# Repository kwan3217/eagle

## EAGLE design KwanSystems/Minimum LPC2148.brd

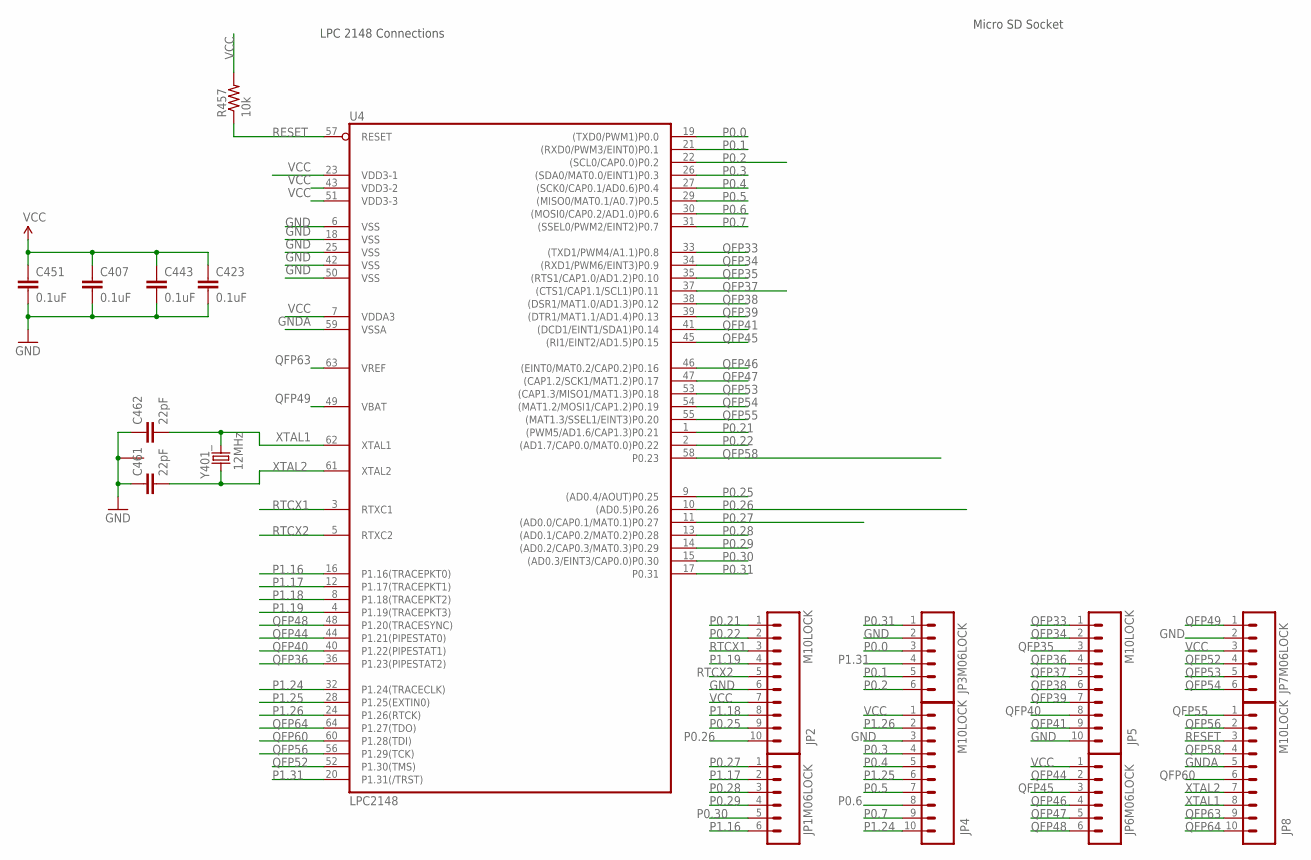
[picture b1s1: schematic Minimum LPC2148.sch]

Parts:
C407, C423, C443, C451: 0.1uF; 0402-CAP
C461, C462: 22pF; 0402-CAP
JP1, JP3, JP6, JP7: M06LOCK; 1X06_LOCK
JP2, JP4, JP5, JP8: M10LOCK; 1X10_LOCK
R457: 10k; 0402-RES
U4: LPC2148; SQFP-S-10X10-64
Y401: 12MHz; CRYSTAL_SMD

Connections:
GND: C407.2, C423.2, C443.2, C451.2, C461.1, C462.1, JP2.6, JP3.2, JP4.3, JP5.10, JP7.2, U4.6 (VSS), U4.18 (VSS), U4.25 (VSS), U4.42 (VSS), U4.50 (VSS), Y401.2 (1), Y401.4 (1)
GNDA: JP8.5, U4.59 (VSSA)
P0.0: JP3.3, U4.19 ((TXD0/PWM1)P0.0)
P0.1: JP3.5, U4.21 ((RXD0/PWM3/EINT0)P0.1)
P0.2: JP3.6, U4.22 ((SCL0/CAP0.0)P0.2)
P0.3: JP4.4, U4.26 ((SDA0/MAT0.0/EINT1)P0.3)
P0.4: JP4.5, U4.27 ((SCK0/CAP0.1/AD0.6)P0.4)
P0.5: JP4.7, U4.29 ((MISO0/MAT0.1/A0.7)P0.5)
P0.6: JP4.8, U4.30 ((MOSI0/CAP0.2/AD1.0)P0.6)
P0.7: JP4.9, U4.31 ((SSEL0/PWM2/EINT2)P0.7)
P0.21: JP2.1, U4.1 ((PWM5/AD1.6/CAP1.3)P0.21)
P0.22: JP2.2, U4.2 ((AD1.7/CAP0.0/MAT0.0)P0.22)
P0.25: JP2.9, U4.9 ((AD0.4/AOUT)P0.25)
P0.26: JP2.10, U4.10 ((AD0.5)P0.26)
P0.27: JP1.1, U4.11 ((AD0.0/CAP0.1/MAT0.1)P0.27)
P0.28: JP1.3, U4.13 ((AD0.1/CAP0.2/MAT0.2)P0.28)
P0.29: JP1.4, U4.14 ((AD0.2/CAP0.3/MAT0.3)P0.29)
P0.30: JP1.5, U4.15 ((AD0.3/EINT3/CAP0.0)P0.30)
P0.31: JP3.1, U4.17 (P0.31)
P1.16: JP1.6, U4.16 (P1.16(TRACEPKT0))
P1.17: JP1.2, U4.12 (P1.17(TRACEPKT1))
P1.18: JP2.8, U4.8 (P1.18(TRACEPKT2))
P1.19: JP2.4, U4.4 (P1.19(TRACEPKT3))
P1.24: JP4.10, U4.32 (P1.24(TRACECLK))
P1.25: JP4.6, U4.28 (P1.25(EXTIN0))
P1.26: JP4.2, U4.24 (P1.26(RTCK))
P1.31: JP3.4, U4.20 (P1.31(/TRST))
QFP33: JP5.1, U4.33 ((TXD1/PWM4/A1.1)P0.8)
QFP34: JP5.2, U4.34 ((RXD1/PWM6/EINT3)P0.9)
QFP35: JP5.3, U4.35 ((RTS1/CAP1.0/AD1.2)P0.10)
QFP36: JP5.4, U4.36 (P1.23(PIPESTAT2))
QFP37: JP5.5, U4.37 ((CTS1/CAP1.1/SCL1)P0.11)
QFP38: JP5.6, U4.38 ((DSR1/MAT1.0/AD1.3)P0.12)
QFP39: JP5.7, U4.39 ((DTR1/MAT1.1/AD1.4)P0.13)
QFP40: JP5.8, U4.40 (P1.22(PIPESTAT1))
QFP41: JP5.9, U4.41 ((DCD1/EINT1/SDA1)P0.14)
QFP44: JP6.2, U4.44 (P1.21(PIPESTAT0))
QFP45: JP6.3, U4.45 ((RI1/EINT2/AD1.5)P0.15)
QFP46: JP6.4, U4.46 ((EINT0/MAT0.2/CAP0.2)P0.16)
QFP47: JP6.5, U4.47 ((CAP1.2/SCK1/MAT1.2)P0.17)
QFP48: JP6.6, U4.48 (P1.20(TRACESYNC))
QFP49: JP7.1, U4.49 (VBAT)
QFP52: JP7.4, U4.52 (P1.30(TMS))
QFP53: JP7.5, U4.53 ((CAP1.3/MISO1/MAT1.3)P0.18)
QFP54: JP7.6, U4.54 ((MAT1.2/MOSI1/CAP1.2)P0.19)
QFP55: JP8.1, U4.55 ((MAT1.3/SSEL1/EINT3)P0.20)
QFP56: JP8.2, U4.56 (P1.29(TCK))
QFP58: JP8.4, U4.58 (P0.23)
QFP60: JP8.6, U4.60 (P1.28(TDI))
QFP63: JP8.9, U4.63 (VREF)
QFP64: JP8.10, U4.64 (P1.27(TDO))
RESET: JP8.3, R457.1, U4.57 (RESET)
RTCX1: JP2.3, U4.3 (RTXC1)
RTCX2: JP2.5, U4.5 (RTXC2)
VCC: C407.1, C423.1, C443.1, C451.1, JP2.7, JP4.1, JP6.1, JP7.3, R457.2, U4.7 (VDDA3), U4.23 (VDD3-1), U4.43 (VDD3-2), U4.51 (VDD3-3)
XTAL1: C462.2, JP8.8, U4.62 (XTAL1), Y401.3 (2)
XTAL2: C461.2, JP8.7, U4.61 (XTAL2), Y401.1

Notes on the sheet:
Micro SD Socket
LPC 2148 Connections

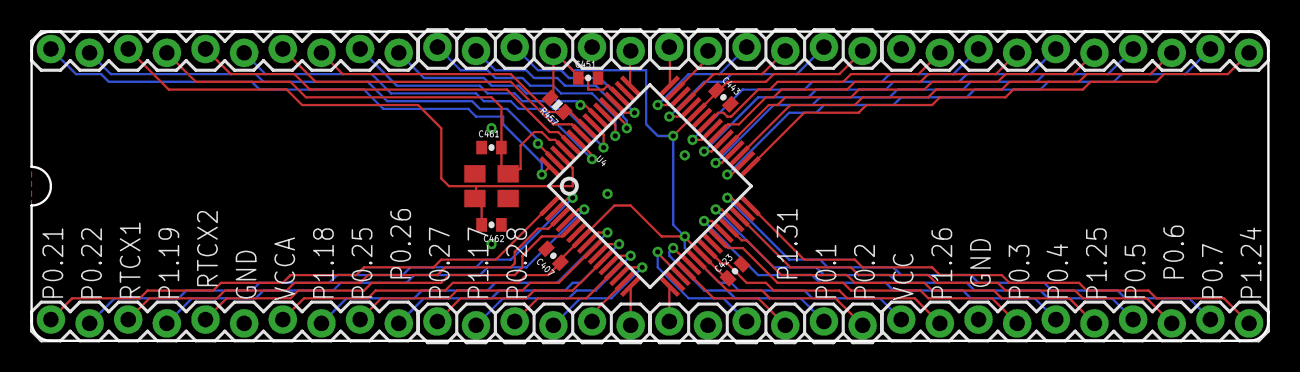
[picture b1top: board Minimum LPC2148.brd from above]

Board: 2 copper layers, 81.3 x 20.3 mm, 17 parts (0 on the bottom side), 57 nets.

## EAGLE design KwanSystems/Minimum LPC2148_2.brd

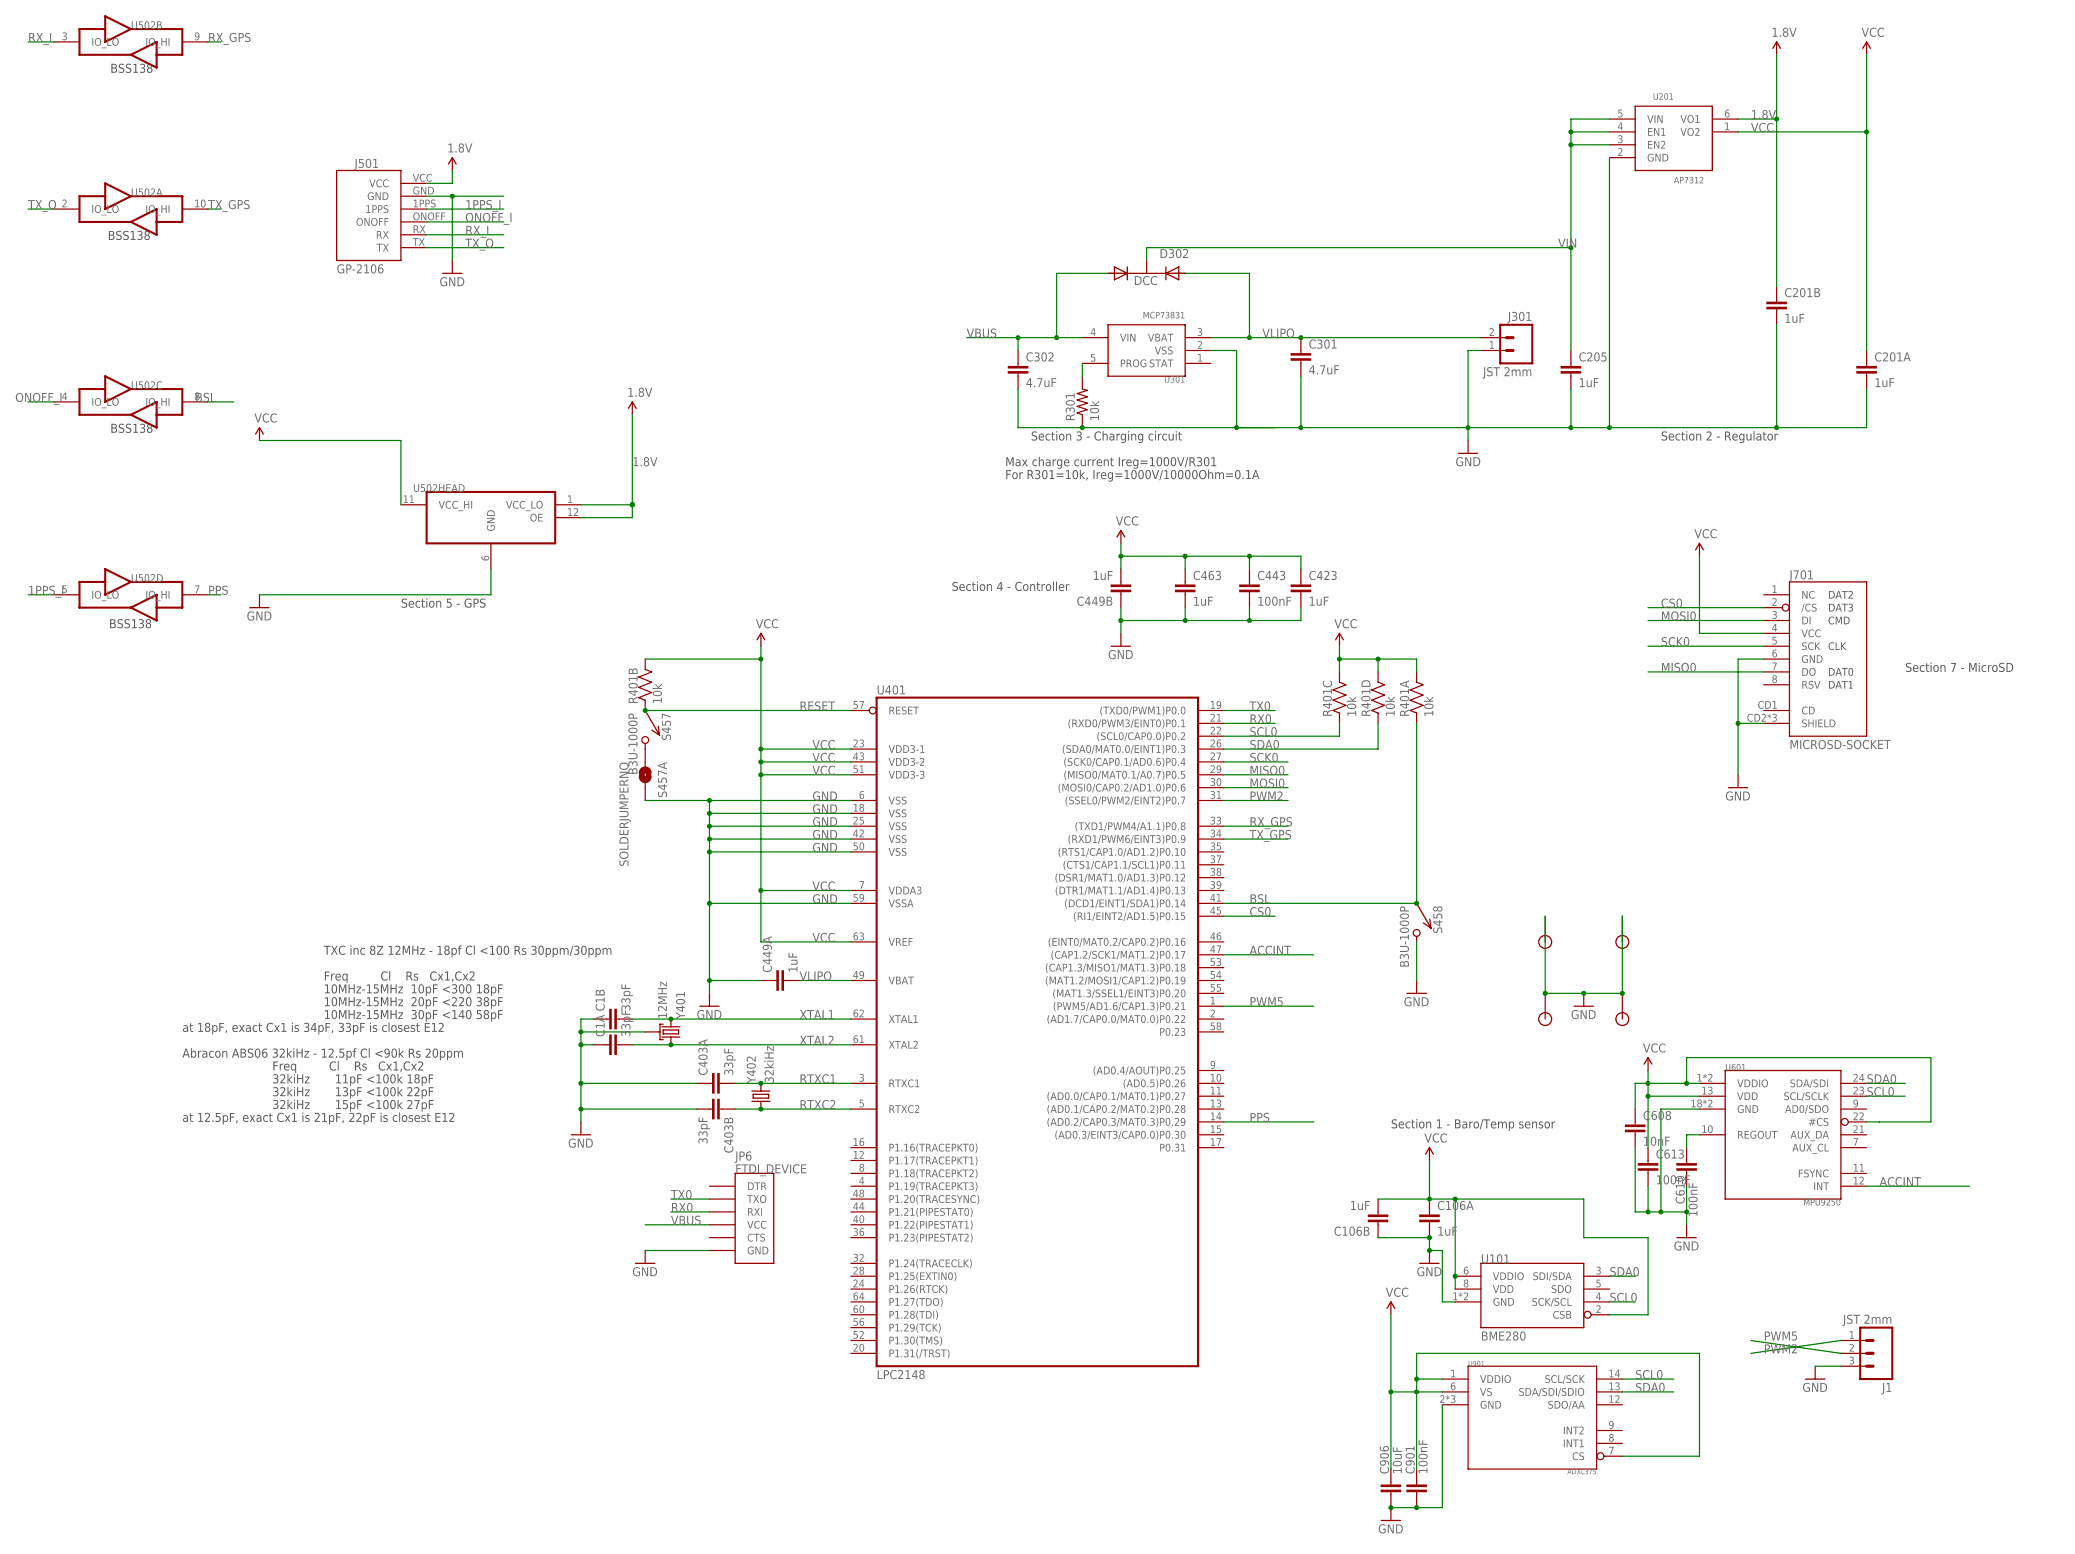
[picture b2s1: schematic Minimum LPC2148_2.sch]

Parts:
C1, C403: 33pF; CKCM25
C106, C201, C449: 1uF; CKCM25
C205, C423, C463: 1uF; 0402-CAP; DIGIKEY 445-4114-1-ND
C301, C302: 4.7uF; 0402-CAP; DIGIKEY 445-7395-1-ND
C443, C610, C613, C901: 100nF; 0402-CAP; DIGIKEY 445-1265-1-ND
C608: 10nF; 0402-CAP; DIGIKEY 445-1257-1-ND
C906: 10uF; 0603-CAP; DIGIKEY 445-7486-1-ND
D302: DCC; SOT-23-3; DIGIKEY 568-6500-1-ND
J1: JST 2mm; 1X03_NO_SILK; DIGIKEY 455-1749-1-ND
J301: JST 2mm; 1X02_NO_SILK; DIGIKEY 455-1749-1-ND
J501: GP-2106
J701: MICROSD-SOCKET; MICROSD-SOCKET-PP; DIGIKEY 101-00581-59-1-ND
JP1, JP2, JP4, JP5: STANDOFF; DIGIKEY $NOPART
JP6: FTDI_DEVICE; FTDI_DEVICE_SIDE
R301: 10k; 0402-RES; DIGIKEY P10.0KLCT-ND
R401: 10k; CRA04; DIGIKEY CRA4S810KCT-ND
S457, S458: B3U-1000P; DIGIKEY SW1020CT-ND
S457A: SOLDERJUMPERNO; SJ_2S-NO; DIGIKEY $NOPART
U101: BME280
U201: AP7312; SOT-23-6
U301: MCP73831; SOT-23-5; DIGIKEY 576-1910-1-ND
U401: LPC2148; SQFP-S-10X10-64; DIGIKEY 568-1765-ND
U502: TXB0104RUT; R-PUQFN-N12
U601: MPU9250; LQFN_3MM_3MM
U901: ADXL375
Y401: 12MHz; CRYSTAL_SMD_2MM_2_5MM; DIGIKEY 887-1487-1-ND
Y402: 32kiHz; ABS06; DIGIKEY 535-10104-1-ND

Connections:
1.8V: C201.2 (1), J501.VCC, U201.6 (VO1), U502.1 (VCC_LO), U502.12 (OE)
1PPS_I: J501.1PPS, U502.5 (IO_LO)
ACCINT: U401.47 ((CAP1.2/SCK1/MAT1.2)P0.17), U601.12 (INT)
BSL: R401.1, S458.P$1 (1), U401.41 ((DCD1/EINT1/SDA1)P0.14), U502.8 (IO_HI)
CS0: J701.2 (/CS), U401.45 ((RI1/EINT2/AD1.5)P0.15)
GND: C1.1, C1.2 (1), C106.2 (1), C106.4 (2), C201.3 (2), C201.4 (2), C205.2, C301.2, C302.2, C403.1, C403.3 (2), C423.2, C443.2, C449.1, C449.2 (1), C463.2, C608.2, C610.2, C613.2, C901.2, C906.2, J1.3, J301.1, J501.GND, J701.6 (GND), J701.CD2 (SHIELD), J701.GND1 (SHIELD), J701.GND3 (SHIELD), JP1.P$1, JP2.P$1, JP4.P$1, JP5.P$1, JP6.P$6 (GND), R301.1, S457A.2, S458.P$2 (2), U101.1 (GND), U101.7 (GND), U201.2 (GND), U301.2 (VSS), U401.6 (VSS), U401.18 (VSS), U401.25 (VSS), U401.42 (VSS), U401.50 (VSS), U401.59 (VSSA), U502.6 (GND), U601.18 (GND), U601.20 (GND), U901.2 (GND), U901.4 (GND), U901.5 (GND), Y401.2 (GND), Y401.4 (GND)
MISO0: J701.7 (DO), U401.29 ((MISO0/MAT0.1/A0.7)P0.5)
MOSI0: J701.3 (DI), U401.30 ((MOSI0/CAP0.2/AD1.0)P0.6)
unnamed: R301.2, U301.5 (PROG)
unnamed: S457.P$2 (2), S457A.1
unnamed: C610.1, U601.10 (REGOUT)
ONOFF_I: J501.ONOFF, U502.4 (IO_LO)
PPS: U401.14 ((AD0.2/CAP0.3/MAT0.3)P0.29), U502.7 (IO_HI)
PWM2: J1.1, U401.31 ((SSEL0/PWM2/EINT2)P0.7)
PWM5: J1.2, U401.1 ((PWM5/AD1.6/CAP1.3)P0.21)
RESET: R401.2 (1), S457.P$1 (1), U401.57 (RESET)
RTXC1: C403.4 (2), U401.3 (RTXC1), Y402.2
RTXC2: C403.2 (1), U401.5 (RTXC2), Y402.1
RX0: JP6.P$3 (RXI), U401.21 ((RXD0/PWM3/EINT0)P0.1)
RX_GPS: U401.33 ((TXD1/PWM4/A1.1)P0.8), U502.9 (IO_HI)
RX_I: J501.RX, U502.3 (IO_LO)
SCK0: J701.5 (SCK), U401.27 ((SCK0/CAP0.1/AD0.6)P0.4)
SCL0: R401.3 (1), U101.4 (SCK/SCL), U401.22 ((SCL0/CAP0.0)P0.2), U601.23 (SCL/SCLK), U901.14 (SCL/SCK)
SDA0: R401.4 (1), U101.3 (SDI/SDA), U401.26 ((SDA0/MAT0.0/EINT1)P0.3), U601.24 (SDA/SDI), U901.13 (SDA/SDI/SDIO)
TX0: JP6.P$2 (TXO), U401.19 ((TXD0/PWM1)P0.0)
TX_GPS: U401.34 ((RXD1/PWM6/EINT3)P0.9), U502.10 (IO_HI)
TX_O: J501.TX, U502.2 (IO_LO)
VBUS: C302.1, D302.1 (A1), JP6.P$4 (VCC), U301.4 (VIN)
VCC: C106.1, C106.3 (2), C201.1, C423.1, C443.1, C449.3 (2), C463.1, C608.1, C613.1, C901.1, C906.1, J701.4 (VCC), R401.5 (2), R401.6 (2), R401.7 (2), R401.8 (2), U101.2 (CSB), U101.6 (VDDIO), U101.8 (VDD), U201.1 (VO2), U401.7 (VDDA3), U401.23 (VDD3-1), U401.43 (VDD3-2), U401.51 (VDD3-3), U401.63 (VREF), U502.11 (VCC_HI), U601.1 (VDDIO), U601.8 (VDDIO), U601.13 (VDD), U601.22 (#CS), U901.1 (VDDIO), U901.6 (VS), U901.7 (CS)
VIN: C205.1, D302.3 (K), U201.3 (EN2), U201.4 (EN1), U201.5 (VIN)
VLIPO: C301.1, C449.4 (2), D302.2 (A2), J301.2, U301.3 (VBAT), U401.49 (VBAT)
XTAL1: C1.3 (2), U401.62 (XTAL1), Y401.3 (2)
XTAL2: C1.4 (2), U401.61 (XTAL2), Y401.1

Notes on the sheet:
Section 2 - Regulator
Section 4 - Controller
Section 7 - MicroSD
Section 1 - Baro/Temp sensor
Freq Cl Rs Cx1,Cx2
10MHz-15MHz 10pF <300 18pF
10MHz-15MHz 20pF <220 38pF
10MHz-15MHz 30pF <140 58pF
TXC inc 8Z 12MHz - 18pf Cl <100 Rs 30ppm/30ppm
at 18pF, exact Cx1 is 34pF, 33pF is closest E12
32kiHz 11pF <100k 18pF
32kiHz 13pF <100k 22pF
32kiHz 15pF <100k 27pF
Abracon ABS06 32kiHz - 12.5pf Cl <90k Rs 20ppm
at 12.5pF, exact Cx1 is 21pF, 22pF is closest E12
Section 3 - Charging circuit
Max charge current Ireg=1000V/R301
For R301=10k, Ireg=1000V/10000Ohm=0.1A
BSS138
Section 5 - GPS

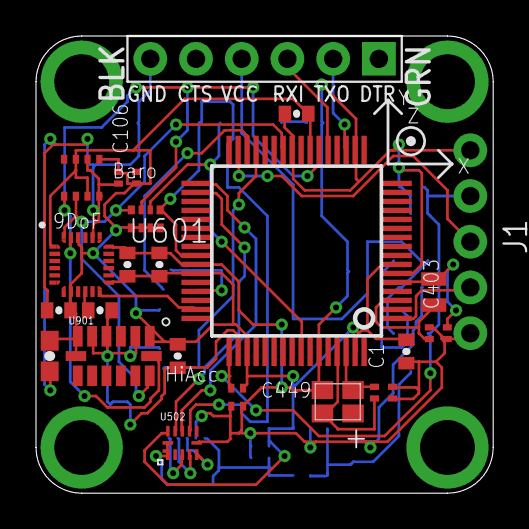
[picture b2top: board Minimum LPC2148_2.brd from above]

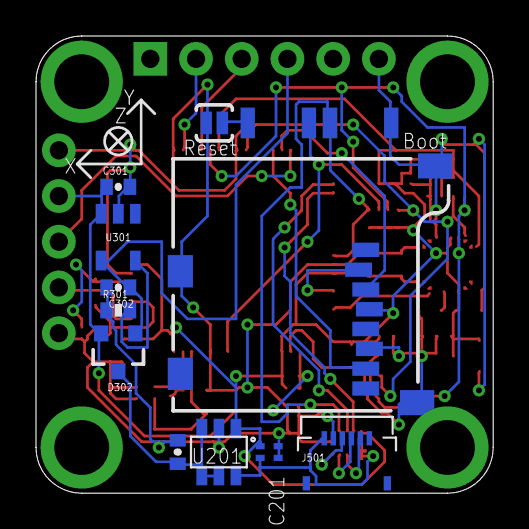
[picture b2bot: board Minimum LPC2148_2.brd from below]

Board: 2 copper layers, 25.4 x 25.4 mm, 41 parts (14 on the bottom side), 33 nets.

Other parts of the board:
U$4: AXES

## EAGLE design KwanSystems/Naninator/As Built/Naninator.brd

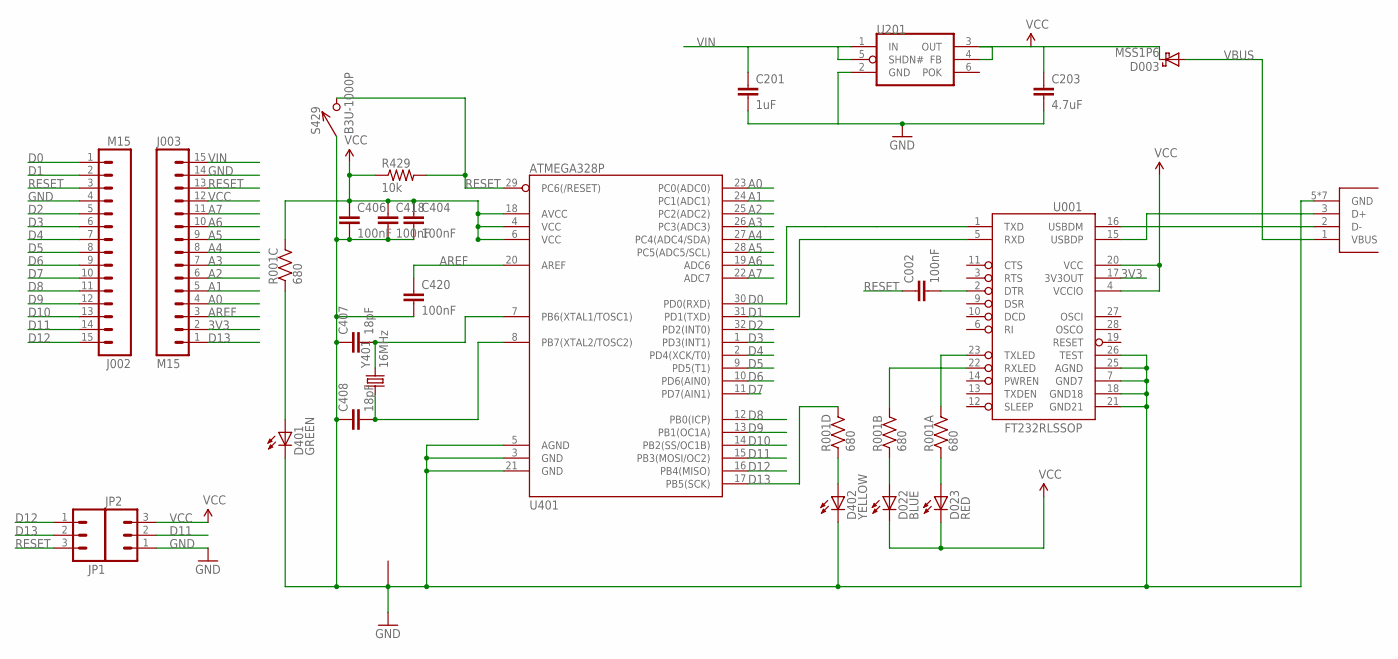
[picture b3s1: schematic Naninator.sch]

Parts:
C002, C404, C406, C418, C420: 100nF; 0402-CAP; DIGIKEY 445-1268-1-ND
C201: 1uF; 0402-CAP; DIGIKEY 445-1415-1-ND
C203: 4.7uF; 0402-CAP; DIGIKEY 445-7395-1-ND
C407, C408: 18pF; 0402-CAP; DIGIKEY 445-1238-1-ND
D003: MSS1P6; MICROSMP; DIGIKEY MSS1P6-M3/89AGICT-ND
D022: BLUE; LED-0603; DIGIKEY 350-2037-1-ND
D023: RED; LED-0603; DIGIKEY 754-1359-1-ND
D401: GREEN; LED-0603; DIGIKEY 350-2036-1-ND
D402: YELLOW; LED-0603; DIGIKEY 754-1124-1-ND
J001: USB_MICROB_JST; UB-MC5BR3-SD204-4S; DIGIKEY 455-2562-1-ND
J002, J003: M15; 1X15; DIGIKEY $NOPART
JP1, JP2: M03PTH; 1X03; DIGIKEY $NOPART
R001: 680; CRA04; DIGIKEY CRA4S8680CT-ND
R429: 10k; 0402-RES; DIGIKEY P10.0KLCT-ND
S429: B3U-1000P
U001: FT232RLSSOP; SSOP28DB; DIGIKEY 768-1007-1-ND
U201: MAX8881; SOT-23-6; DIGIKEY MAX8881EUT50+TCT-ND
U401: ATMEGA328P; TQFP32-08; DIGIKEY ATMEGA328P-15AZCT-ND
Y401: 16MHz; CRYSTAL_SMD_2MM_2_5MM; DIGIKEY 478-6955-1-ND

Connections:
3V3: J003.2, U001.17 (3V3OUT)
A0: J003.4, U401.23 (PC0(ADC0))
A1: J003.5, U401.24 (PC1(ADC1))
A2: J003.6, U401.25 (PC2(ADC2))
A3: J003.7, U401.26 (PC3(ADC3))
A4: J003.8, U401.27 (PC4(ADC4/SDA))
A5: J003.9, U401.28 (PC5(ADC5/SCL))
A6: J003.10, U401.19 (ADC6)
A7: J003.11, U401.22 (ADC7)
AREF: C420.1, J003.3, U401.20 (AREF)
D0: J002.1, U001.1 (TXD), U401.30 (PD0(RXD))
D1: J002.2, U001.5 (RXD), U401.31 (PD1(TXD))
D2: J002.5, U401.32 (PD2(INT0))
D3: J002.6, U401.1 (PD3(INT1))
D4: J002.7, U401.2 (PD4(XCK/T0))
D5: J002.8, U401.9 (PD5(T1))
D6: J002.9, U401.10 (PD6(AIN0))
D7: J002.10, U401.11 (PD7(AIN1))
D8: J002.11, U401.12 (PB0(ICP))
D9: J002.12, U401.13 (PB1(OC1A))
D10: J002.13, U401.14 (PB2(SS/OC1B))
D11: J002.14, JP2.2, U401.15 (PB3(MOSI/OC2))
D12: J002.15, JP1.1, U401.16 (PB4(MISO))
D13: J003.1, JP1.2, R001.5 (2), U401.17 (PB5(SCK))
DTR#: C002.2, U001.2 (DTR)
GND: C201.2, C203.2, C404.2, C406.2, C407.1, C408.1, C418.2, C420.2, D401.C, D402.C, J001.5 (GND), J001.P$6 (GND), J001.P$7 (GND), J001.P$8 (GND), J001.P$9 (GND), J001.P$10 (GND), J001.P$11 (GND), J002.4, J003.14, JP2.1, S429.P$1 (1), U001.7 (GND7), U001.18 (GND18), U001.21 (GND21), U001.25 (AGND), U001.26 (TEST), U201.2 (GND), U401.3 (GND), U401.5 (AGND), U401.21 (GND), Y401.2 (1), Y401.4 (1)
unnamed: C407.2, U401.7 (PB6(XTAL1/TOSC1)), Y401.3 (2)
unnamed: C408.2, U401.8 (PB7(XTAL2/TOSC2)), Y401.1
unnamed: J001.3 (D+), U001.15 (USBDP)
unnamed: J001.2 (D-), U001.16 (USBDM)
unnamed: D401.A, R001.3 (1)
unnamed: D402.A, R001.4 (1)
unnamed: D023.A, R001.1
unnamed: D022.A, R001.2 (1)
RESET: C002.1, J002.3, J003.13, JP1.3, R429.2, S429.P$2 (2), U401.29 (PC6(/RESET))
RXLED1: R001.7 (2), U001.22 (RXLED)
TXLED1: R001.8 (2), U001.23 (TXLED)
VBUS: D003.A, J001.1 (VBUS)
VCC: C203.1, C404.1, C406.1, C418.1, D003.K, D022.C, D023.C, J003.12, JP2.3, R001.6 (2), R429.1, U001.4 (VCCIO), U001.20 (VCC), U201.3 (OUT), U201.4 (FB), U401.4 (VCC), U401.6 (VCC), U401.18 (AVCC)
VIN: C201.1, J003.15, U201.1 (IN), U201.5 (SHDN#)

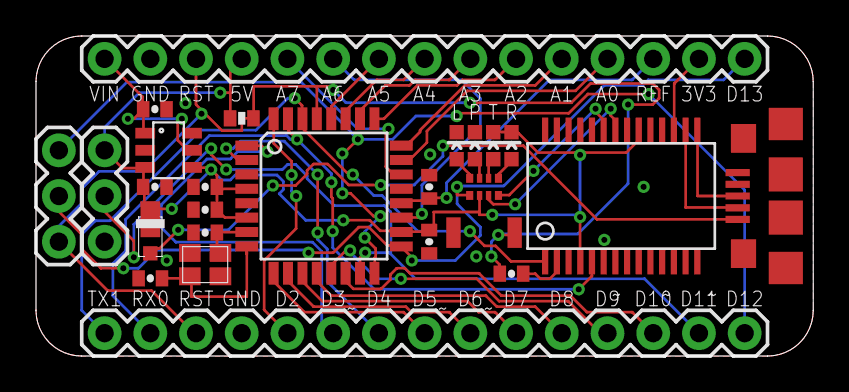
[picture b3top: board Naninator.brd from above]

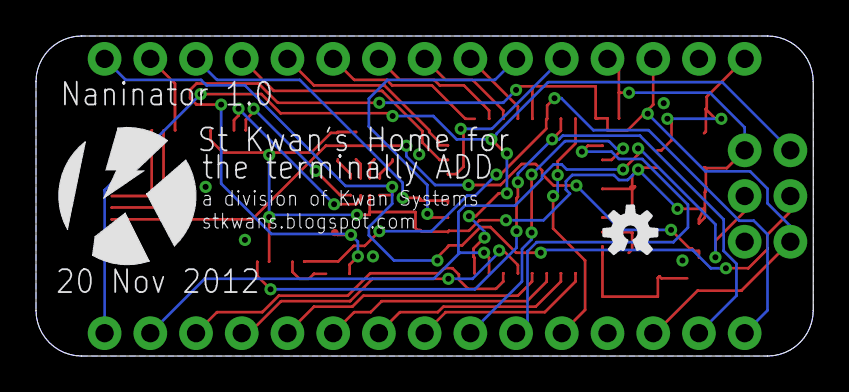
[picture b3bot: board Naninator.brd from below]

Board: 2 copper layers, 43.2 x 17.8 mm, 28 parts (2 on the bottom side), 40 nets.

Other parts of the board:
U$1: KWAN_CIRCLE
U$2: OSHW-LOGO-S

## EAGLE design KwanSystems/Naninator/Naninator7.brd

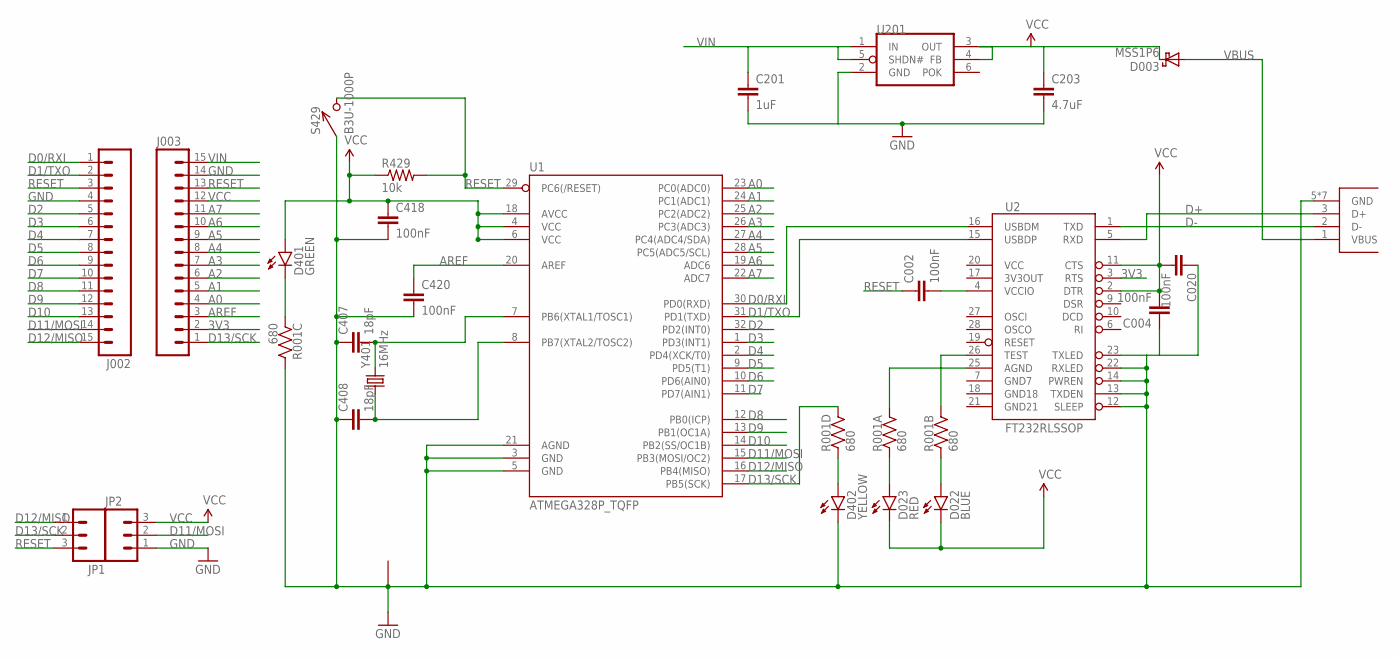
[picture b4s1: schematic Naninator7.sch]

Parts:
C002, C004, C020, C418, C420: 100nF; 0402-CAP; DIGIKEY 445-1268-1-ND
C201: 1uF; 0402-CAP; DIGIKEY 445-1415-1-ND
C203: 4.7uF; 0402-CAP; DIGIKEY 445-7395-1-ND
C407, C408: 18pF; 0402-CAP; DIGIKEY 445-1238-1-ND
D003: MSS1P6; MICROSMP; DIGIKEY MSS1P6-M3/89AGICT-ND
D022: BLUE; LED-0603; DIGIKEY 350-2037-1-ND
D023: RED; LED-0603; DIGIKEY 754-1359-1-ND
D401: GREEN; LED-0603; DIGIKEY 350-2036-1-ND
D402: YELLOW; LED-0603; DIGIKEY 754-1124-1-ND
J001: USB_MICROB_JSTFCI; USB-MICROB-CONN-09505; DIGIKEY 455-2562-1-ND
J002, J003: M15; 1X15; DIGIKEY $NOPART
JP1, JP2: M03PTH; 1X03; DIGIKEY $NOPART
R001: 680; CRA04; DIGIKEY CRA4S8680CT-ND
R429: 10k; 0402-RES; DIGIKEY P10.0KLCT-ND
S429: B3U-1000P
U1: ATMEGA328P_TQFP; TQFP32-08
U2: FT232RLSSOP; SSOP28DB
U201: MAX8881; SOT-23-6; DIGIKEY MAX8881EUT50+TCT-ND
Y401: 16MHz; CRYSTAL_SMD_2MM_2_5MM; DIGIKEY 478-6955-1-ND

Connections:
3V3: J003.2, U2.3 (RTS)
A0: J003.4, U1.23 (PC0(ADC0))
A1: J003.5, U1.24 (PC1(ADC1))
A2: J003.6, U1.25 (PC2(ADC2))
A3: J003.7, U1.26 (PC3(ADC3))
A4: J003.8, U1.27 (PC4(ADC4/SDA))
A5: J003.9, U1.28 (PC5(ADC5/SCL))
A6: J003.10, U1.19 (ADC6)
A7: J003.11, U1.22 (ADC7)
AREF: C420.1, J003.3, U1.20 (AREF)
D0/RXI: J002.1, U1.30 (PD0(RXD)), U2.16 (USBDM)
D1/TXO: J002.2, U1.31 (PD1(TXD)), U2.15 (USBDP)
D2: J002.5, U1.32 (PD2(INT0))
D3: J002.6, U1.1 (PD3(INT1))
D4: J002.7, U1.2 (PD4(XCK/T0))
D5: J002.8, U1.9 (PD5(T1))
D6: J002.9, U1.10 (PD6(AIN0))
D7: J002.10, U1.11 (PD7(AIN1))
D8: J002.11, U1.12 (PB0(ICP))
D9: J002.12, U1.13 (PB1(OC1A))
D10: J002.13, U1.14 (PB2(SS/OC1B))
D11/MOSI: J002.14, JP2.2, U1.15 (PB3(MOSI/OC2))
D12/MISO: J002.15, JP1.1, U1.16 (PB4(MISO))
D13/SCK: J003.1, JP1.2, R001.5 (2), U1.17 (PB5(SCK))
D+: J001.3 (D+), U2.5 (RXD)
D-: J001.2 (D-), U2.1 (TXD)
DTR#: C002.2, U2.4 (VCCIO)
GND: C004.1, C020.1, C201.2, C203.2, C407.1, C408.1, C418.2, C420.2, D402.C, J001.5 (GND), J001.P1 (GND), J001.P2 (GND), J001.P3 (GND), J001.P4 (GND), J001.P5 (GND), J001.P6 (GND), J002.4, J003.14, JP2.1, R001.6 (2), S429.P$1 (1), U1.3 (GND), U1.5 (GND), U1.21 (AGND), U2.12 (SLEEP), U2.13 (TXDEN), U2.14 (PWREN), U2.22 (RXLED), U2.23 (TXLED), U201.2 (GND), Y401.2 (1), Y401.4 (1)
GND7: U2.7 (GND7)
GND18: U2.18 (GND18)
GND21: U2.21 (GND21)
unnamed: C407.2, U1.7 (PB6(XTAL1/TOSC1)), Y401.3 (2)
unnamed: C408.2, U1.8 (PB7(XTAL2/TOSC2)), Y401.1
unnamed: D401.C, R001.3 (1)
unnamed: D022.A, R001.2 (1)
unnamed: D023.A, R001.1
unnamed: D402.A, R001.4 (1)
RESET: C002.1, J002.3, J003.13, JP1.3, R429.2, S429.P$2 (2), U1.29 (PC6(/RESET))
RXLED1: R001.8 (2), U2.25 (AGND)
TXLED1: R001.7 (2), U2.26 (TEST)
VBUS: D003.A, J001.1 (VBUS)
VCC: C004.2, C020.2, C203.1, C418.1, D003.K, D022.C, D023.C, D401.A, J003.12, JP2.3, R429.1, U1.4 (VCC), U1.6 (VCC), U1.18 (AVCC), U2.2 (DTR), U2.11 (CTS), U2.20 (VCC), U201.3 (OUT), U201.4 (FB)
VIN: C201.1, J003.15, U201.1 (IN), U201.5 (SHDN#)

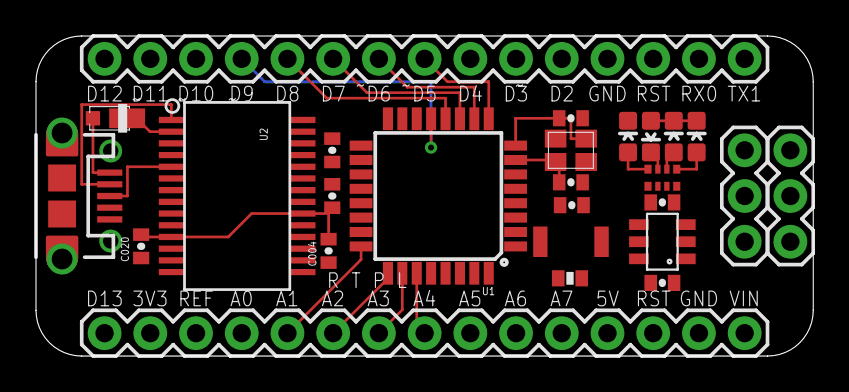
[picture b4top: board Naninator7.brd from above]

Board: 2 copper layers, 43.2 x 17.8 mm, 26 parts (0 on the bottom side), 40 nets.

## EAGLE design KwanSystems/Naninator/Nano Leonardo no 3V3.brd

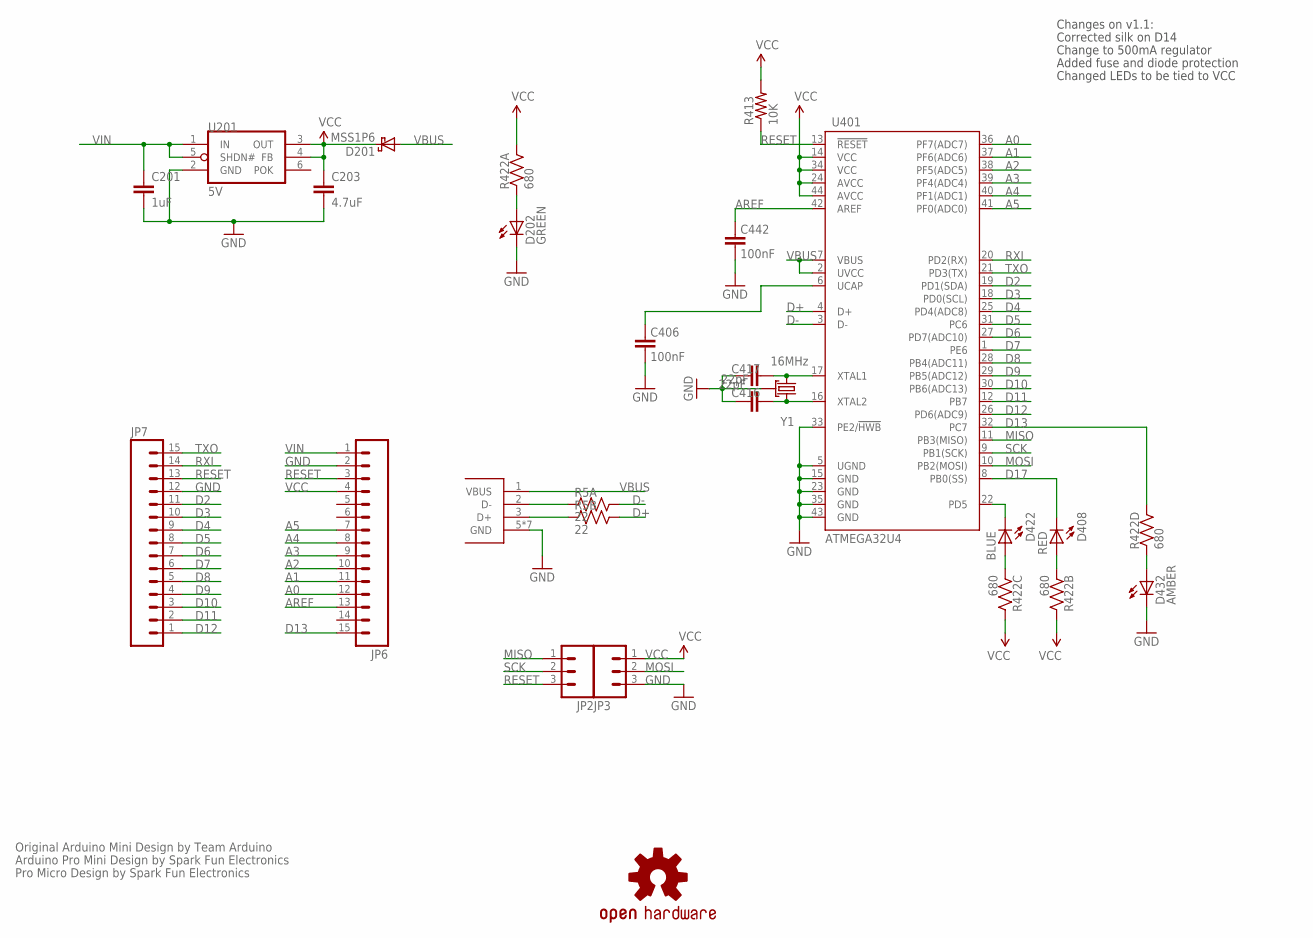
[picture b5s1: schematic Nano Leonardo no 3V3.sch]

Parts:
C201: 1uF; 0402-CAP; DIGIKEY 445-1415-1-ND
C203: 4.7uF; 0402-CAP; DIGIKEY 445-7395-1-ND
C406, C442: 100nF; 0402-CAP
C416, C417: 22pF; 0402-CAP
D201: MSS1P6; MICROSMP; DIGIKEY MSS1P6-M3/89AGICT-ND
D202: GREEN; LED-0603
D408: RED; LED-0603
D422: BLUE; LED-0603
D432: AMBER; LED-0603
JP2, JP3: M031X03_NO_SILK; 1X03_NO_SILK
JP6, JP7: M15; 1X15
R5: 22; CRA02
R413: 10K; 0402-RES
R422: 680; CRA04
U201: 5V; SOT-23-6; DIGIKEY MAX8881EUT50+TCT-ND
U401: ATMEGA32U4; QFN-44-NOPAD
U$3: OSHW-LOGOS; OSHW-LOGO-S
X1: USB_MICROB_JSTGCT; USB_MICROB_3075
Y1: 16MHz; CRYSTAL_SMD_2MM_2_5MM

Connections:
A0: JP6.12, U401.36 (PF7(ADC7))
A1: JP6.11, U401.37 (PF6(ADC6))
A2: JP6.10, U401.38 (PF5(ADC5))
A3: JP6.9, U401.39 (PF4(ADC4))
A4: JP6.8, U401.40 (PF1(ADC1))
A5: JP6.7, U401.41 (PF0(ADC0))
AREF: C442.2, JP6.13, U401.42 (AREF)
D2: JP7.11, U401.19 (PD1(SDA))
D3: JP7.10, U401.18 (PD0(SCL))
D4: JP7.9, U401.25 (PD4(ADC8))
D5: JP7.8, U401.31 (PC6)
D6: JP7.7, U401.27 (PD7(ADC10))
D7: JP7.6, U401.1 (PE6)
D8: JP7.5, U401.28 (PB4(ADC11))
D9: JP7.4, U401.29 (PB5(ADC12))
D10: JP7.3, U401.30 (PB6(ADC13))
D11: JP7.2, U401.12 (PB7)
D12: JP7.1, U401.26 (PD6(ADC9))
D13: JP6.15, R422.5 (2), U401.32 (PC7)
D17: D408.C, U401.8 (PB0(SS))
D+: R5.3 (2), U401.4 (D+)
D-: R5.4 (2), U401.3 (D-)
GND: C201.2, C203.2, C406.1, C416.2, C417.2, C442.1, D202.C, D432.C, JP3.3, JP6.2, JP7.12, U201.2 (GND), U401.5 (UGND), U401.15 (GND), U401.23 (GND), U401.33 (PE2/!HWB), U401.35 (GND), U401.43 (GND), X1.5 (GND), X1.P$1 (GND), X1.P$2 (GND), X1.P$3 (GND), X1.P$4 (GND), X1.P$8 (GND), X1.P$10 (GND), Y1.2 (GND), Y1.4 (GND)
MISO: JP2.1, U401.11 (PB3(MISO))
MOSI: JP3.2, U401.10 (PB2(MOSI))
unnamed: D422.A, R422.3 (1)
unnamed: D408.A, R422.2 (1)
unnamed: D432.A, R422.4 (1)
unnamed: C406.2, U401.6 (UCAP)
unnamed: R5.1, X1.2 (D-)
unnamed: R5.2 (1), X1.3 (D+)
unnamed: D202.A, R422.1
RESET: JP2.3, JP6.3, JP7.13, R413.1, U401.13 (!RESET)
RXI: JP7.14, U401.20 (PD2(RX))
SCK: JP2.2, U401.9 (PB1(SCK))
TXLED: D422.C, U401.22 (PD5)
TXO: JP7.15, U401.21 (PD3(TX))
VBUS: D201.A, U401.2 (UVCC), U401.7 (VBUS), X1.1 (VBUS)
VCC: C203.1, D201.K, JP3.1, JP6.4, R413.2, R422.6 (2), R422.7 (2), R422.8 (2), U201.3 (OUT), U201.4 (FB), U401.14 (VCC), U401.24 (AVCC), U401.34 (VCC), U401.44 (AVCC)
VIN: C201.1, JP6.1, U201.1 (IN), U201.5 (SHDN#)
XTAL1: C417.1, U401.17 (XTAL1), Y1.1
XTAL2: C416.1, U401.16 (XTAL2), Y1.3 (2)

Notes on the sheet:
Original Arduino Mini Design by Team Arduino
Arduino Pro Mini Design by Spark Fun Electronics
Pro Micro Design by Spark Fun Electronics
Changes on v1.1:
Corrected silk on D14
Change to 500mA regulator
Added fuse and diode protection
Changed LEDs to be tied to VCC

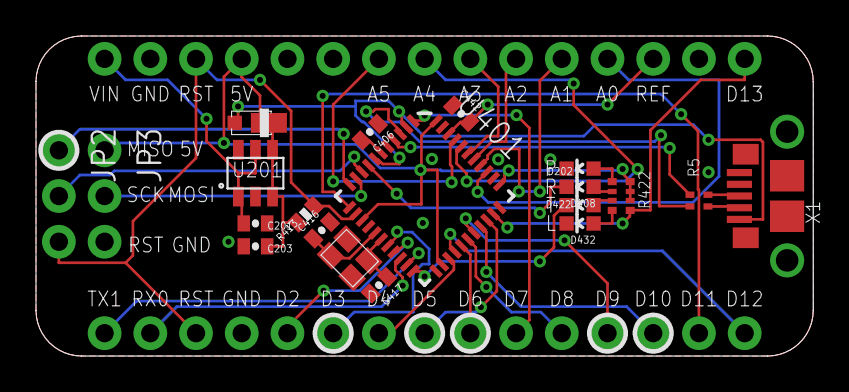
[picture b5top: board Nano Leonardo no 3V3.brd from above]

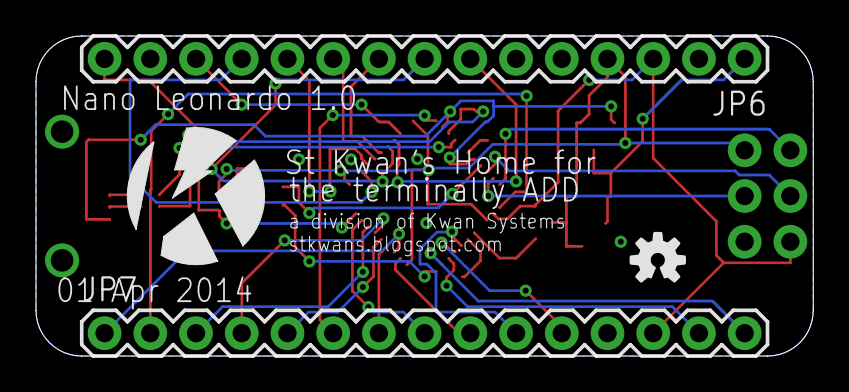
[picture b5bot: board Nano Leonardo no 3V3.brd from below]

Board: 2 copper layers, 43.2 x 17.8 mm, 24 parts (4 on the bottom side), 42 nets.

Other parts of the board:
U$1: KWAN_CIRCLE

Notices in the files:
parts and their libraries:
SparkFun-Connectors: Licensing: CC v3.0 Share-Alike You are welcome to use this library for commercial purposes.
SparkFun-DigitalIC: Licensing: Creative Commons ShareAlike 4.0 International - https://creativecommons.org/licenses/by-sa/4.0
